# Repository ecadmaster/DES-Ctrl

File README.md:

# Dust Extraction System Control (DES-Ctrl)

Solución de hardware y firmware de código abierto diseñada para replicar y controlar la interfaz de extracción de polvo mediante aspiración en las trazadoras de placas de circuito impreso **LPKF ProtoMat**, utilizando sistemas de aspiración comerciales asequibles.

Desarrollado como proyecto académico para la asignatura **Laboratorio de Electrónica III** en la Escuela de Ingeniería Eléctrica de la **Universidad de Los Andes (ULA)**, Mérida, Venezuela.

---

## Descripción general del proyecto

Los sistemas originales LPKF ProtoMat emplean una unidad de extracción de polvo por vacío sincronizada, controlada mediante una interfaz serie UART conectada directamente a la fresadora. Cuando las unidades de extracción originales no están presentes o no se encuentran disponibles, su sustitución por hardware específico resulta económicamente prohibitiva.

**DES-Ctrl** resuelve este desafío mediante un enfoque de hardware de dos etapas:
1. **PCB1 (Sniffer / Man-in-the-Middle):** Una interfaz de diagnóstico (pasiva/activa) que cuenta con conectores DB9 macho/hembra y puntos de prueba para interceptar, registrar y analizar los paquetes de comunicación UART entre una LPKF ProtoMat y su sistema original de extracción de polvo.
2. **PCB2 (Controlador y etapa de potencia):** Una placa con microcontrolador integrado, equipada con detección de cruce por cero y conmutación mediante triac/tiristor, diseñada para regular la velocidad y la potencia de una aspiradora comercial estándar y los estados operativos de la máquina LPKF.

## PCB1 Sniffer

| Schematic | Layout | 3D-Model |
| :--------: | :--------: | :--------: |
|  |  |   |

---

## Repository Structure

```text
DES-Ctrl/
├── hardware/
│   ├── pcb1_sniffer/       # Interceptor UART con salida TTL
│   └── pcb2_controller/    # Microcontrolador y etapa de potencia con detección de cruce por cero
├── firmware/               # Firmware de MCU para la decodificación y control de motores
├── docs/                   # Notas técnicas, capturas de protocolos y esquemas
└── LICENSE                 # MIT Open Source License

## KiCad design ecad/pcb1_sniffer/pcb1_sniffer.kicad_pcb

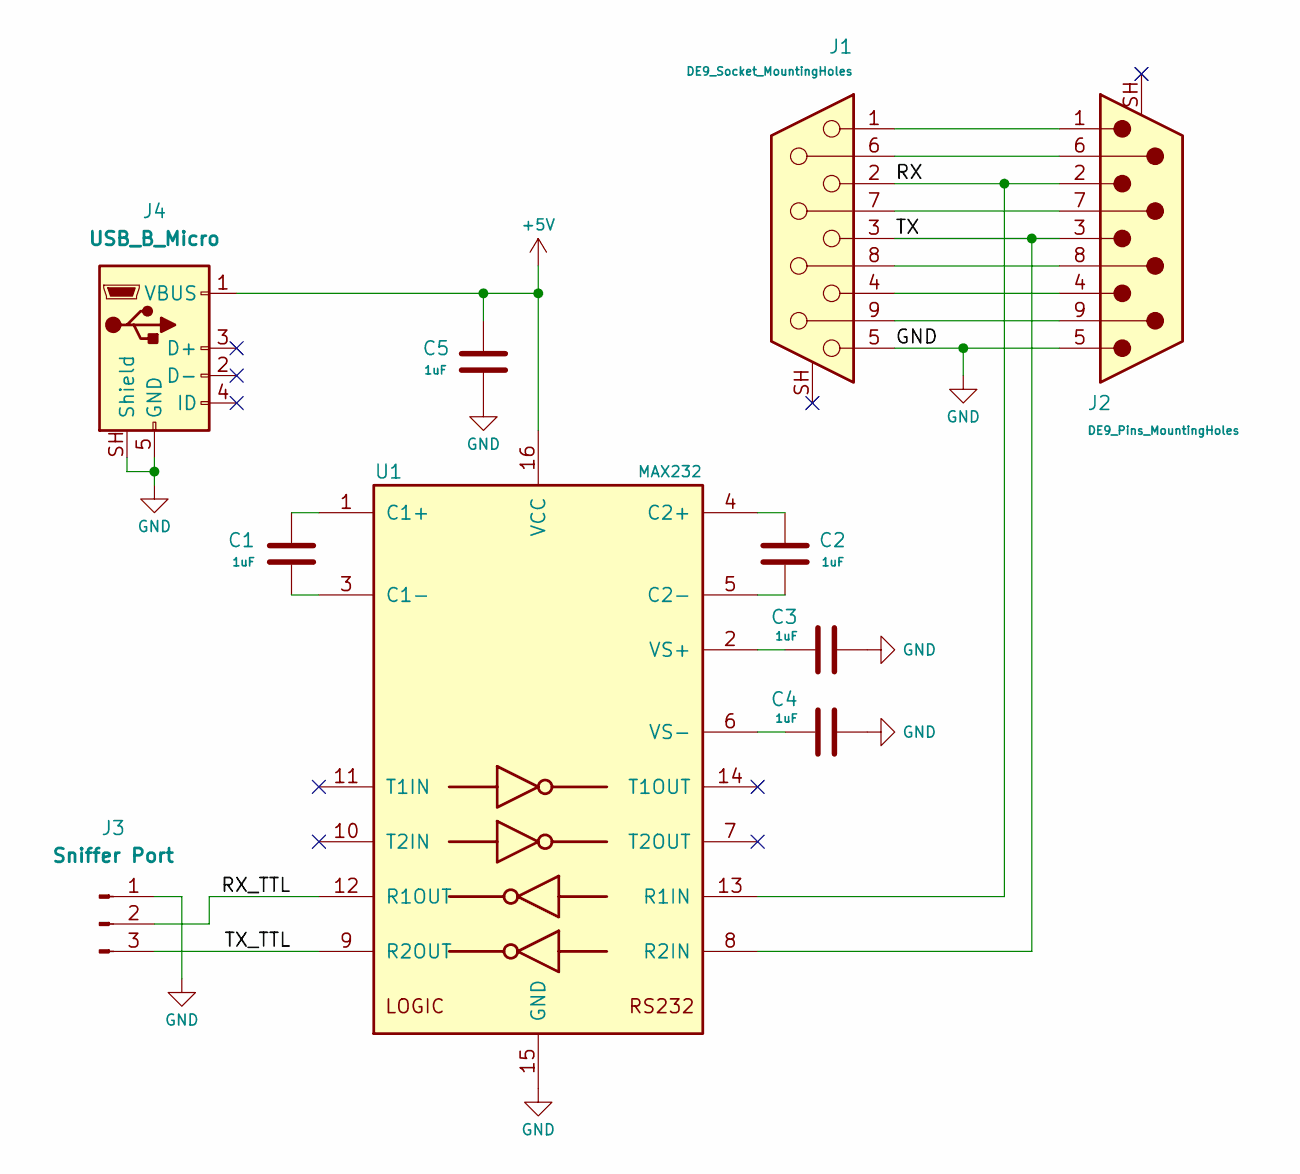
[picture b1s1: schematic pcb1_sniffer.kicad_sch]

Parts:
C1: 1uF; C_Disc_D4.3mm_W1.9mm_P5.00mm
C2, C3, C4, C5: 1uF; C_Disc_D3.0mm_W1.6mm_P2.50mm
J1: DE9_Socket_MountingHoles; DSUB-9_Socket_Horizontal_P2.77x2.84mm_EdgePinOffset4.94mm_H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
J2: DE9_Pins_MountingHoles; DSUB-9_Pins_Horizontal_P2.77x2.84mm_EdgePinOffset4.94mm_Hou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
J3: Sniffer Port; PinHeader_1x03_P2.54mm_Vertical
J4: USB_B_Micro; USB_Micro-B_Molex_47346-0001
U1: MAX232; DIP-16_W7.62mm_LongPads

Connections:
+5V: C5.1, J4.1 (VBUS), U1.16 (VCC)
/RX: J1.2, J2.2, U1.13 (R1IN)
/RX_TTL: J3.2, U1.12 (R1OUT)
/TX: J1.3, J2.3, U1.8 (R2IN)
/TX_TTL: J3.3, U1.9 (R2OUT)
GND: C3.2, C4.2, C5.2, J1.5, J2.5, J3.1, J4.5 (GND), J4.SH (Shield), U1.15 (GND)
unnamed: J1.1, J2.1
unnamed: J1.4, J2.4
unnamed: J1.6, J2.6
unnamed: J1.7, J2.7
unnamed: J1.8, J2.8
unnamed: J1.9, J2.9
unnamed: C1.1, U1.1 (C1+)
unnamed: C1.2, U1.3 (C1-)
unnamed: C2.1, U1.4 (C2+)
unnamed: C2.2, U1.5 (C2-)
unnamed: C3.1, U1.2 (VS+)
unnamed: C4.1, U1.6 (VS-)

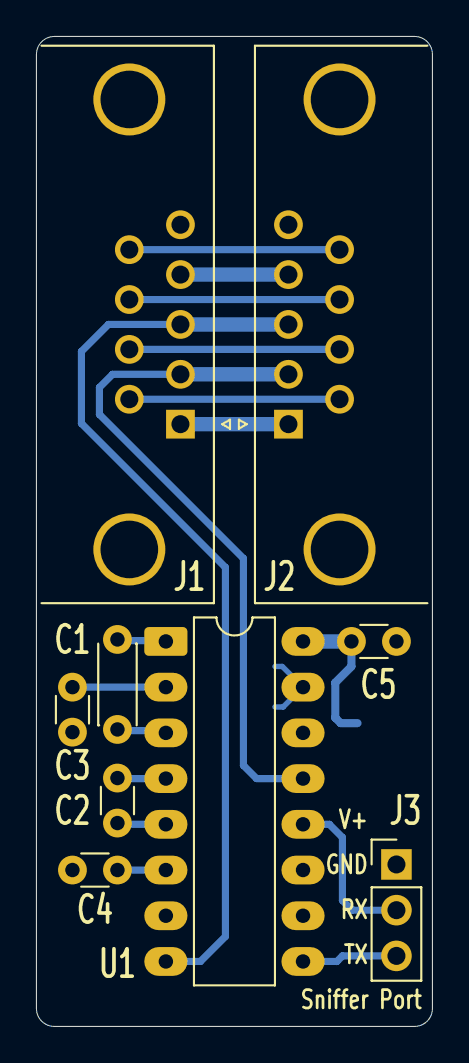
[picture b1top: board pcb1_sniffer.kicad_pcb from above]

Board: 2 copper layers, 22.0 x 55.0 mm, 10 parts (1 on the bottom side), 18 nets.
